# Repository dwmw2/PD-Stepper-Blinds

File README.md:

# PD-Stepper-Blinds

ESPHome-based automatic blind control system using the [PD-Stepper](https://github.com/joshr120/PD-Stepper) controller board by ThingsbyJosh.com.

## Overview

This project provides a complete solution for automating window blinds with precise stepper motor control. It includes 3D-printable mounting hardware, a custom power distribution PCB, and ESPHome configuration for seamless Home Assistant integration.

## Hardware

### Components

- **PD-Stepper Kit** - ESP32-based stepper motor controller (includes board, encoder magnet, aluminium spacer and heatsunk)
- **Stepper Motor** - NEMA 17 or compatible
- **Custom Power PCB** - Distributes power to the PD-Stepper board via spring terminals connected to internal pads
- **3D-Printed Mounting Hardware** - Complete blind mounting assembly
- **M3 Hex Standoffs and Nuts** - For assembly ([example](https://www.amazon.co.uk/dp/B08FZKLYSB))
- **M3 Countersunk Bolts, 15mm and 22.5mm** - For mounting ([example](https://www.amazon.co.uk/dp/B0CPDQJ7ZF))
- **JST-PH 2.0mm Connectors** - 3-pin connectors for power PCB ([example](https://www.amazon.co.uk/dp/B0CDG95RDT))
- **2mm Acrylic Rod** - For light guides ([example](https://www.amazon.co.uk/dp/B0DQ1757SP))

### Power Distribution

Power is supplied through a custom PCB that connects to internal pads on the PD-Stepper board using spring terminals, eliminating the need for external connectors.

## 3D Design

The mounting hardware consists of multiple printed parts that work together to create a complete blind mounting assembly.

### Parts

**Motor Housing and Gear**
- **BasePlate** - Main mounting base
- **Outer** - Outer housing component
- **Inner** - Inner housing component
- **Cover** - Top cover
- **Gear** - Drive gear for blind mechanism

**Installation Template**
- **Motor Cavity Template** - Template for positioning screw holes and motor cutout in the window frame

**PCB Assembly Jig**
- **JigOuter** - Assembly jig outer piece
- **JigSpacer** - Assembly jig spacer (for soldering socket onto PCB)

### Design Files

- **Source File** - `3d-design/BlindMount.FCStd` (FreeCAD format)
- **STL Files** - Individual parts in `3d-design/STL/`
- **3MF Files** - Individual parts in `3d-design/3mf/`

## Assembly

### 1. Power PCB Preparation

See [power-pcb/README.md](power-pcb/README.md) for PCB assembly instructions.

| Power PCB | Assembled PCB |
|-----------|---------------|
|  |  |

### 2. Outer Assembly

- Prepare the 3D-printed Outer piece by pushing two half-width M3 nuts into diagonally opposed holes, then pushing the power PCB into its slot on the other side.
- Attach the PD-Stepper board to the aluminium spacer using the sticky heat transfer pad, and loosely place the Cover piece on top.
- Apply the Outer piece to the back of the PD-Stepper board so that the spring terminals make contact with the power and NTC pads.
- Screw together using two 15mm countersunk bolts.
- Cut sections of the acrylic rod to use as light guides, and push them gently into the holes for the blue and red LEDs.
- Finally, affix the heatsink to the full assembly through the gap in the Cover.

| Exploded View | Bottom | Top |
|---------------|--------|-----|
|  |  |  |

### 3. Build Motor Cable

- Using JST-PH 2.0 connectors, build a 4-pin to 6-pin cable which works for your motor, matching either the straight-through or crossover cables from the PD-Stepper kit which won't be long enough to reach.
- Test the motor and cable using your completed outer assembly.

### 4. Motor Housing

- Pass the motor cable through the cable hole, then attach the Base Plate to the motor using the hex standoffs. Use two short (5-6mm) standoffs in the corners where the Outer assembly is screwed together, and two longer (8mm) standoffs in the corners which will be used to screw the Inner to this piece.
- You will have to turn the standoffs by a few degrees to the correct orientation such that the Inner piece fits over them. The Inner piece itself can be used as a spanner for that purpose. The Inner piece then pushes over the standoffs and guide posts.
- Offer the Outer assembly up to this to check that it all fits together.

| Aligning the hex standoffs | Motor Assembly |
|----------------------------|----------------|
|  |  |

### 5. Gear Installation

- Push the Gear onto the motor shaft, pushing it fully home until the centre of the Gear is aligned with the centre of the guides in the Inner (and Outer) pieces and the cord will flow freely.
- The centre of the Gear is fully round for 2.5mm at the back and then has a flat part. This is fully parameterised in the spreadsheet in the FreeCAD model, if you need to adjust it or make the Inner piece thicker to allow for a longer shaft.
- You may also need to trim the motor shaft so that there is sufficient space to install the encoder magnet. The easiest way to do this is to install a Gear and then use a Dremel to cut through both Gear and motor shaft at the right point. I kept the motor turning as I did this to ensure a smooth cut.
- Push the encoder magnet from the PD-Stepper kit into the front of the Gear as shown. It should push fully home and be a relatively snug fit. If you have a metallic blind cord, note that the magnet may sometimes prefer attaching itself to the blind cord rather than staying in the Gear where you put it.

| Trimmed gear shaft | Gear with magnet |
|--------------------|------------------|
|  |  |

### 6. Final Assembly

- Two 22.5mm bolts go through the other corners of the Outer assembly to secure it to the Base Plate, with the blind cord inside. Bolts of that length are hard to come by; you *may* find that 20mm is just about enough, but I used 25mm bolts and the Dremel.
- The 3-pin JST-PH plug is shown connected to the Power PCB in the Outer Assembly. You may prefer to use all black for the visible part, and/or apply heatshrink. As shown in the images, the pinout is:
  - Black: GND
  - Red: +5V to +20V
  - Yellow: Reed switch, closed to GND when the blind is fully open *(optional)*.

| Assembled Units | Connector Wiring |
|-----------------|------------------|
|  |  |

## Installation

For instructions on mounting the completed assembly into your window frame, see [INSTALLATION.md](INSTALLATION.md).

## Programming

ESPHome configuration examples are provided in the `esphome/` directory. The `landing-blind-1.yaml` file shows a complete configuration with the following substitutions:

- **name** - Device name for ESPHome and Home Assistant
- **encoder_closed_pos** - Full blinds length in encoder counts (adjust to suit your setup)
- **encoder_direction** - Which direction is towards 'closed' (1 or -1)
- **motor_direction** - Motor direction relative to encoder (1 or -1)
- **microsteps** - Microstepping setting for the stepper driver
- **run_current** - Motor run current (e.g., "100m" for 100mA)
- **max_speed** - Maximum motor speed
- **stallguard_threshold** - StallGuard threshold for stall detection
- **pd_voltage** - Power delivery voltage (unused)

On power-up, the controller will assume that the blinds are open. The first time it is asked to open the blinds, it will perform a rehoming operation, running at half-speed until it stalls. It will close the blinds at sunset, and open the blinds at 07:30AM or sunrise, whichever is later.

You can tweak the current, speed and stallguard settings to suit your blinds and motor, so that the stall is detected correctly. The motor_direction may differ for supposedly identical installations, if your motor cables are wired differently. Some notes on calibration are in the top of the [`blind.yaml`](esphome/blind.yaml) file.

The third pin on the power connector is for a reed switch, which connects that GPIO pin to ground when the blind is fully open. This is not necessary, because rehoming works well with properly calibrated stall detection anyway. One thing that a reed switch would allow is for the device to be *sure*, on startup, that it is at the home position and to initiate a rehoming if not. Rehoming on startup is disabled because when starting from the home position, the immediate stall... well, isn't immediate enough, and is noisy.

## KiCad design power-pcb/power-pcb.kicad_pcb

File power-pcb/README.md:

# Power PCB

The custom power distribution PCB is an optional component that provides two key features:

- **Internal Power Delivery** - Supplies power directly to internal pads on the PD-Stepper board via Harwin S1761-42R spring terminals, bypassing the USB-C connector
- **Reed Switch Connection** - Provides a connector for a reed switch to detect when the blinds are fully closed

### Design Files

KiCad project files are located in the `power-pcb/` directory. Gerber and drill files for fabrication are available in `power-pcb/Gerber/`.

You can assemble this yourself, but the spring terminals are hard to solder manually. There are plenty of PCB assembly services which will do it for you; I happened to use JLCPCB. For a walk-through of the JLCPCB ordering process for the uninitiated, see [JLCPCB.md](JLCPCB.md).

## Assembly

The power PCB is designed to make contact with the back of the PD-Stepper board, using the terminals shown.

The JST-PH socket is fitted at right angles to the board with its pins laying flat on the copper, so manufacturers like JLCPCB won't be able to build that. Using the Jig as shown to position the socket and PCB, solder them by hand. Don't do it with the PD-Stepper board in place like in the picture. Sandwich the PCB and socket between the Jig parts and screw it together to hold it in place while you solder.

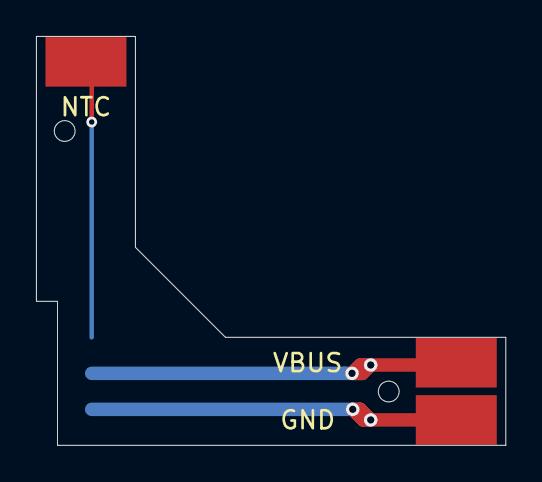
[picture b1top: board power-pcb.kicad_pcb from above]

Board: 2 copper layers, 26.1 x 22.7 mm, 4 parts (1 on the bottom side), 3 nets.

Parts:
GND: Conn_01x01_Pin; HARWIN_S1761-46R
J1: Conn_01x03_Pin; JST_S3B-PH-SM4-TB_LF__SN_
NTC: Conn_01x01_Pin; HARWIN_S1761-46R
VBUS: Conn_01x01_Pin; HARWIN_S1761-46R

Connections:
GND: GND.1, J1.1
unnamed: J1.3, NTC.1
VBUS: J1.2, VBUS.1

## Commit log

2025-11-24 initial import
2025-11-24 Clarify PD-Stepper kit contents
2025-11-24 Move images to images/ directory
2025-11-24 Move power PCB documentation to subdirectory
2025-11-24 Rename step 2 to 'Outer Assembly'
2025-11-24 Clarify diagonal bolt placement in outer assembly
2025-11-24 Add standoff orientation instructions to motor housing
2025-11-24 Add installation documentation
2025-11-24 Add 2mm acrylic rod to components list
2025-11-24 Add light guide installation to outer assembly
2025-11-24 Add Installation section referencing INSTALLATION.md
2025-11-24 Add power connector pinout and reed switch details
2025-11-24 Add power connector pinout image
2025-11-24 Add ESPHome configuration and programming documentation
2025-11-24 Remove Domoticz integration from documentation and config
2025-11-24 Add operational behavior description to programming section
2025-11-24 Add tuning note for motor settings
2025-11-24 Add note about motor_direction variation
2025-11-24 Mark pd_voltage as unused
2025-11-24 Update final installation image
2025-11-24 Add backup files to .gitignore
2025-11-24 Remove backup file from git
2025-11-25 Add reed switch explanation to programming section
2025-11-25 Add CC BY-SA 4.0 and GPLv3 licences
2025-11-25 Add CC BY-SA 4.0 licence badge to README
2025-11-25 Improve assembly instructions and add calibration reference
2025-11-25 Convert all assembly instructions to bullet points
2025-11-25 Consistently capitalize component names and correct Inner/Outer references
2025-11-26 Reimplement cover to avoid importing STL
    Importing and modifying STL annoyed me but was good enough for my own
    use. Now it's published it's even more annoying, *and* the original was
    under GPLv3 so reimplement it.
2025-11-26 Remove extra nut cavity in Outer
    It doesn't matter, and actually allows for longer standoffs to be used in
    the base plate for that corner, but it's probably just confusing.
2025-11-26 Add JLCPCB assembly ordering instructions
2025-11-26 Update README to reference JLCPCB ordering guide
2025-11-27 Reorganize assembly images into compact tables
2025-11-27 Replace Final Assembly image with higher resolution version
2025-11-27 Replace Motor Assembly image with higher resolution version
2025-11-27 Replace Outer Assembly top image with higher resolution version
2025-11-27 Update Motor Assembly image and add Gear with magnet image
2025-11-27 Add Trimmed gear shaft image to Gear Installation section
2025-11-27 Add Assembled PCB image to Power PCB section
2025-11-27 Add Connector Wiring image to Final Assembly section
2025-11-27 Add connector pinout details with nested bullets
2025-11-27 Fix typo
2025-11-28 Improve PCB soldering instructions
2025-12-16 Fix for sunrise after 8am

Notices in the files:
README.md:
License: CC BY-SA 4.0
